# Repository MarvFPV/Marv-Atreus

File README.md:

# Marv Atreus
This is my first attempt at making a keyboard Pcb from scratch.
A Case will also be added.
Very much based on the https://github.com/technomancy/atreus.

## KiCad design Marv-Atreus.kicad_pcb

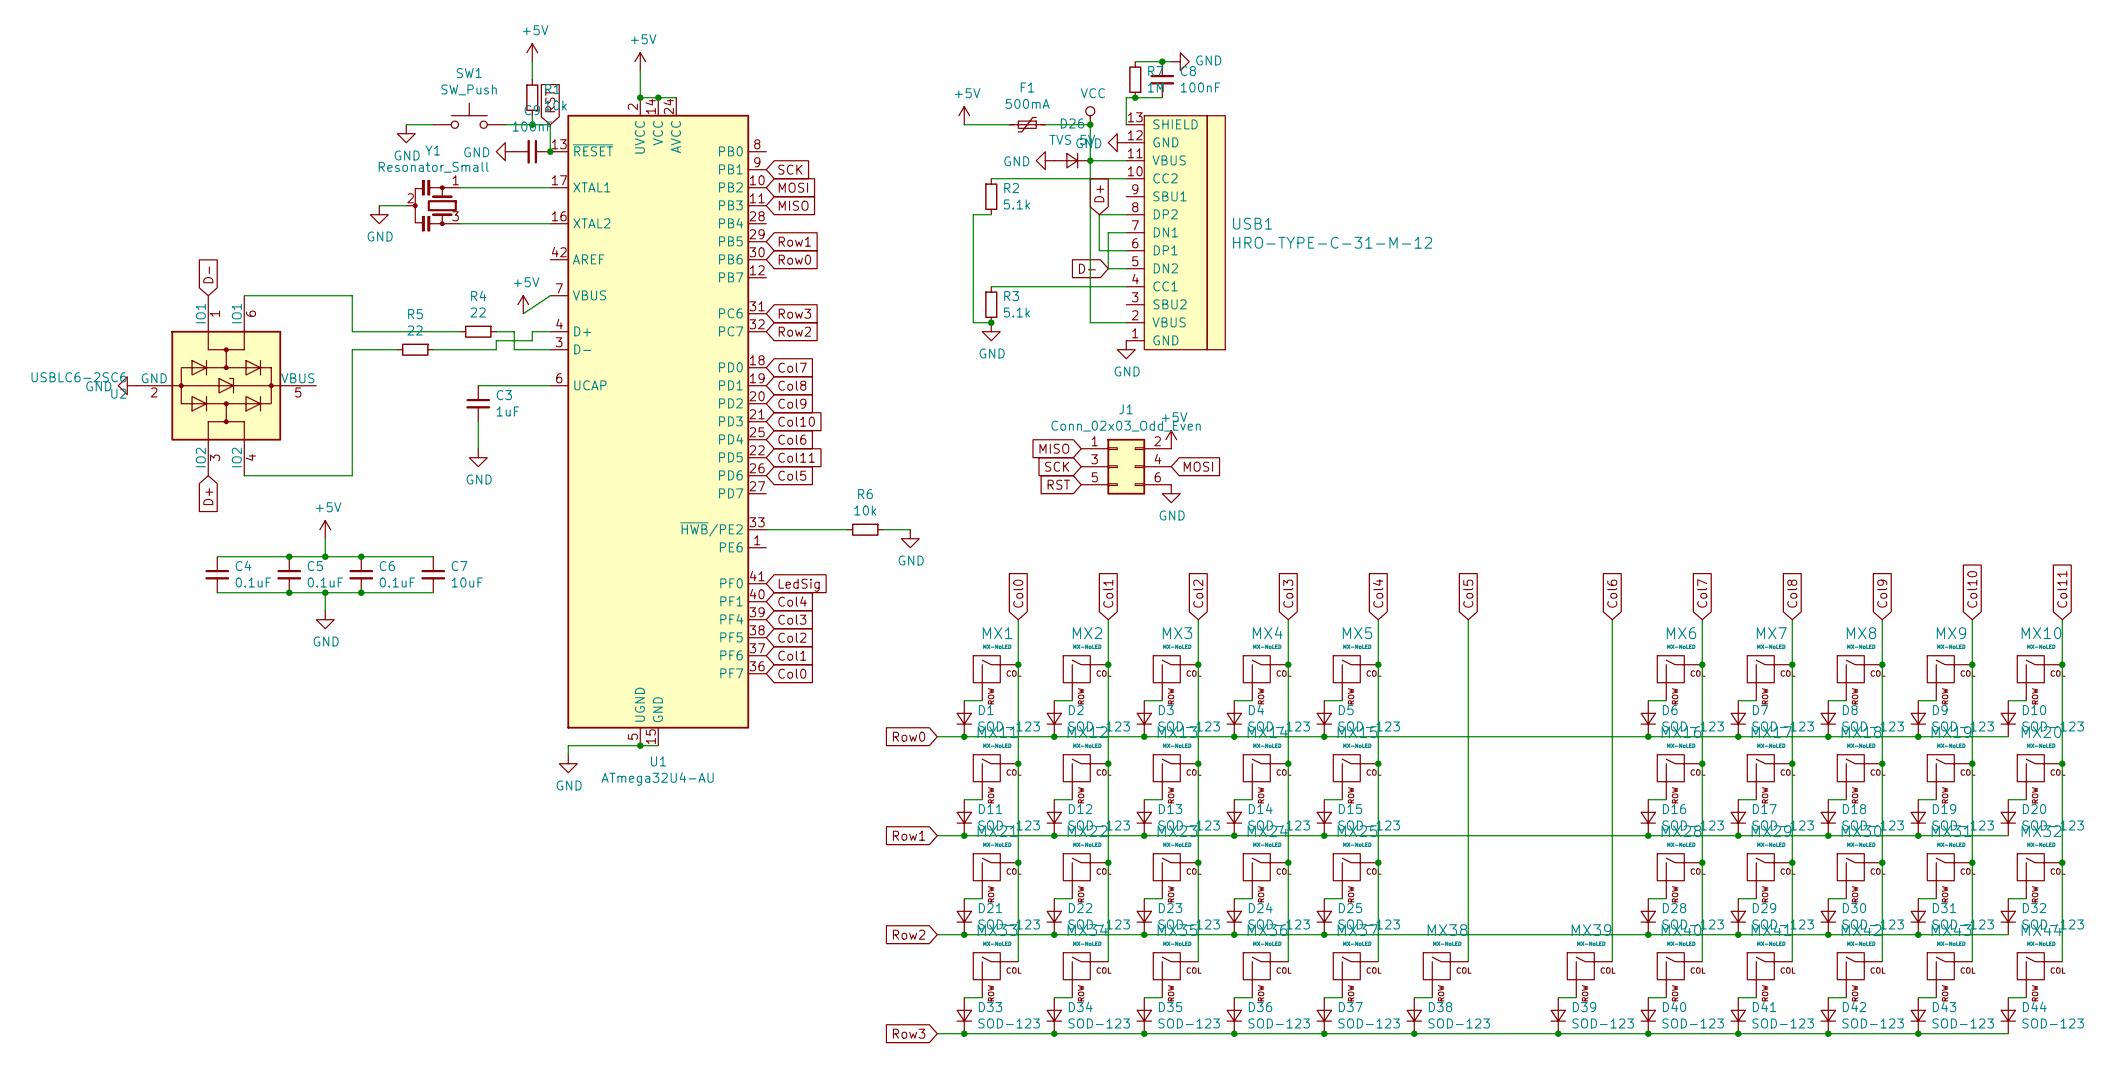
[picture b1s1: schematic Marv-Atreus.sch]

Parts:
C3: 1uF; C_0603_1608Metric
C4, C5, C6: 0.1uF; C_0603_1608Metric
C7: 10uF; C_0603_1608Metric
C8, C9: 100nF; C_0603_1608Metric
D1, D2, D3, D4, D5, D6, D7, D8, D9, D10, D11, D12, D13, D14, D15, D16, D17, D18, D19, D20, D21, D22, D23, D24, D25, D28, D29, D30, D31, D32, D33, D34, D35, D36, D37, D38, D39, D40, D41, D42, D43, D44: SOD-123; D_SOD-123_NoReference
D26: TVS 5V; D_SMB
F1: 500mA; Fuse_1206_3216Metric
J1: Conn_02x03_Odd_Even; PinHeader_2x03_P2.54mm_Vertical
MX1, MX2, MX3, MX4, MX5, MX6, MX7, MX8, MX9, MX10, MX11, MX12, MX13, MX14, MX15, MX16, MX17, MX18, MX19, MX20, MX21, MX22, MX23, MX24, MX25, MX28, MX29, MX30, MX31, MX32, MX33, MX34, MX35, MX36, MX37, MX38, MX39, MX40, MX41, MX42, MX43, MX44: MX-NoLED; MXOnly-1U-NoLED
R1, R6: 10k; R_0603_1608Metric
R2, R3: 5.1k; R_0603_1608Metric
R4, R5: 22; R_0603_1608Metric
R7: 1M; R_0603_1608Metric
SW1: SW_Push; SKQG-1155865
U1: ATmega32U4-AU; TQFP-44_10x10mm_P0.8mm
U2: USBLC6-2SC6; SOT-23-6
USB1: HRO-TYPE-C-31-M-12
Y1: Resonator_Small; Resonator_SMD_muRata_CSTxExxV-3Pin_3.0x1.1mm

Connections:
+5V: C4.1, C5.1, C6.1, C7.1, F1.2, J1.2, R1.1, U1.2 (UVCC), U1.7 (VBUS), U1.14 (VCC), U1.24 (AVCC), U1.34 (VCC), U1.44 (AVCC)
Col0: MX1.1 (COL), MX11.1 (COL), MX21.1 (COL), MX33.1 (COL), U1.36 (PF7)
Col1: MX2.1 (COL), MX12.1 (COL), MX22.1 (COL), MX34.1 (COL), U1.37 (PF6)
Col2: MX3.1 (COL), MX13.1 (COL), MX23.1 (COL), MX35.1 (COL), U1.38 (PF5)
Col3: MX4.1 (COL), MX14.1 (COL), MX24.1 (COL), MX36.1 (COL), U1.39 (PF4)
Col4: MX5.1 (COL), MX15.1 (COL), MX25.1 (COL), MX37.1 (COL), U1.40 (PF1)
Col5: MX38.1 (COL), U1.26 (PD6)
Col6: MX39.1 (COL), U1.25 (PD4)
Col7: MX6.1 (COL), MX16.1 (COL), MX28.1 (COL), MX40.1 (COL), U1.18 (PD0)
Col8: MX7.1 (COL), MX17.1 (COL), MX29.1 (COL), MX41.1 (COL), U1.19 (PD1)
Col9: MX8.1 (COL), MX18.1 (COL), MX30.1 (COL), MX42.1 (COL), U1.20 (PD2)
Col10: MX9.1 (COL), MX19.1 (COL), MX31.1 (COL), MX43.1 (COL), U1.21 (PD3)
Col11: MX10.1 (COL), MX20.1 (COL), MX32.1 (COL), MX44.1 (COL), U1.22 (PD5)
D+: U2.3 (IO2), USB1.6 (DP1), USB1.8 (DP2)
D-: U2.1 (IO1), USB1.5 (DN2), USB1.7 (DN1)
GND: C3.2, C4.2, C5.2, C6.2, C7.2, C8.1, C9.2, D26.2 (A), J1.6, R2.2, R3.2, R6.1, R7.2, SW1.1, U1.5 (UGND), U1.15 (GND), U1.23 (GND), U1.35 (GND), U1.43 (GND), U2.2 (GND), USB1.1 (GND), USB1.12 (GND), Y1.2
LedSig: U1.41 (PF0)
MISO: J1.1, U1.11 (PB3)
MOSI: J1.4, U1.10 (PB2)
unnamed: C3.1, U1.6 (UCAP)
unnamed: C8.2, R7.1, USB1.13 (SHIELD)
unnamed: D1.2 (A), MX1.2 (ROW)
unnamed: D2.2 (A), MX2.2 (ROW)
unnamed: D3.2 (A), MX3.2 (ROW)
unnamed: D4.2 (A), MX4.2 (ROW)
unnamed: D5.2 (A), MX5.2 (ROW)
unnamed: D6.2 (A), MX6.2 (ROW)
unnamed: D7.2 (A), MX7.2 (ROW)
unnamed: D8.2 (A), MX8.2 (ROW)
unnamed: D9.2 (A), MX9.2 (ROW)
unnamed: D10.2 (A), MX10.2 (ROW)
unnamed: D11.2 (A), MX11.2 (ROW)
unnamed: D12.2 (A), MX12.2 (ROW)
unnamed: D13.2 (A), MX13.2 (ROW)
unnamed: D14.2 (A), MX14.2 (ROW)
unnamed: D15.2 (A), MX15.2 (ROW)
unnamed: D16.2 (A), MX16.2 (ROW)
unnamed: D17.2 (A), MX17.2 (ROW)
unnamed: D18.2 (A), MX18.2 (ROW)
unnamed: D19.2 (A), MX19.2 (ROW)
unnamed: D20.2 (A), MX20.2 (ROW)
unnamed: D21.2 (A), MX21.2 (ROW)
unnamed: D22.2 (A), MX22.2 (ROW)
unnamed: D23.2 (A), MX23.2 (ROW)
unnamed: D24.2 (A), MX24.2 (ROW)
unnamed: D25.2 (A), MX25.2 (ROW)
unnamed: D28.2 (A), MX28.2 (ROW)
unnamed: D29.2 (A), MX29.2 (ROW)
unnamed: D30.2 (A), MX30.2 (ROW)
unnamed: D31.2 (A), MX31.2 (ROW)
unnamed: D32.2 (A), MX32.2 (ROW)
unnamed: D33.2 (A), MX33.2 (ROW)
unnamed: D34.2 (A), MX34.2 (ROW)
unnamed: D35.2 (A), MX35.2 (ROW)
unnamed: D36.2 (A), MX36.2 (ROW)
unnamed: D37.2 (A), MX37.2 (ROW)
unnamed: D38.2 (A), MX38.2 (ROW)
unnamed: D39.2 (A), MX39.2 (ROW)
unnamed: D40.2 (A), MX40.2 (ROW)
unnamed: D41.2 (A), MX41.2 (ROW)
unnamed: D42.2 (A), MX42.2 (ROW)
unnamed: D43.2 (A), MX43.2 (ROW)
unnamed: D44.2 (A), MX44.2 (ROW)
unnamed: R2.1, USB1.10 (CC2)
unnamed: R3.1, USB1.4 (CC1)
unnamed: R4.1, U1.3 (D-)
unnamed: R4.2, U2.6 (IO1)
unnamed: R5.1, U1.4 (D+)
unnamed: R5.2, U2.4 (IO2)
unnamed: R6.2, U1.33 (~HWB~/PE2)
unnamed: U1.16 (XTAL2), Y1.3
unnamed: U1.17 (XTAL1), Y1.1
RST: C9.1, J1.5, R1.2, SW1.2, U1.13 (~RESET)
Row0: D1.1 (K), D2.1 (K), D3.1 (K), D4.1 (K), D5.1 (K), D6.1 (K), D7.1 (K), D8.1 (K), D9.1 (K), D10.1 (K), U1.30 (PB6)
Row1: D11.1 (K), D12.1 (K), D13.1 (K), D14.1 (K), D15.1 (K), D16.1 (K), D17.1 (K), D18.1 (K), D19.1 (K), D20.1 (K), U1.29 (PB5)
Row2: D21.1 (K), D22.1 (K), D23.1 (K), D24.1 (K), D25.1 (K), D28.1 (K), D29.1 (K), D30.1 (K), D31.1 (K), D32.1 (K), U1.32 (PC7)
Row3: D33.1 (K), D34.1 (K), D35.1 (K), D36.1 (K), D37.1 (K), D38.1 (K), D39.1 (K), D40.1 (K), D41.1 (K), D42.1 (K), D43.1 (K), D44.1 (K), U1.31 (PC6)
SCK: J1.3, U1.9 (PB1)
VCC: D26.1 (K), F1.1, USB1.2 (VBUS), USB1.11 (VBUS)

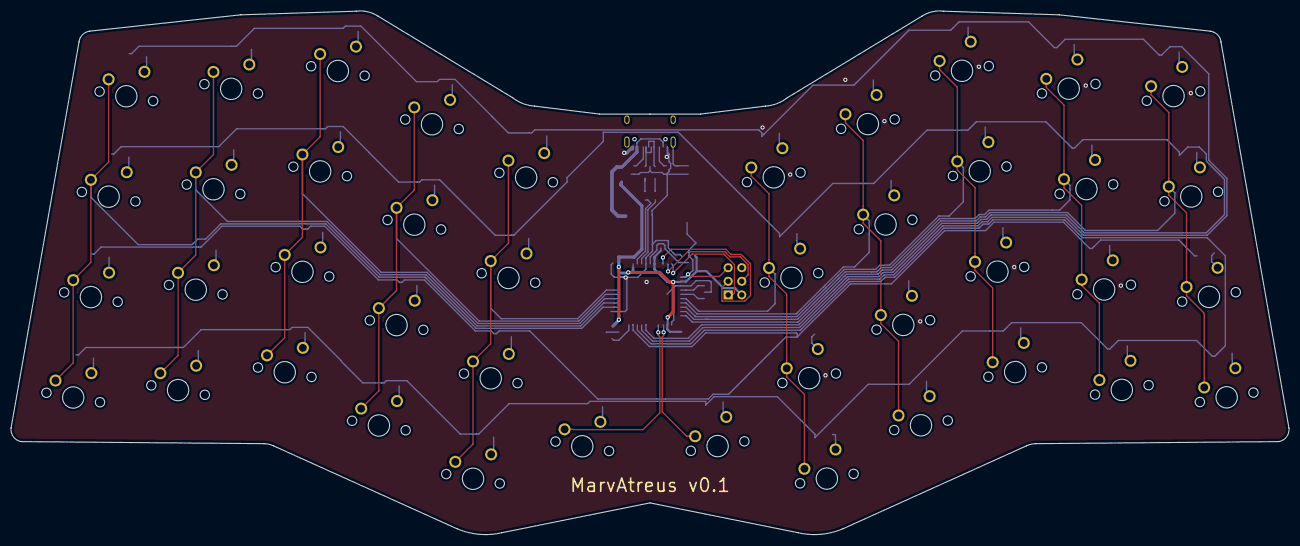
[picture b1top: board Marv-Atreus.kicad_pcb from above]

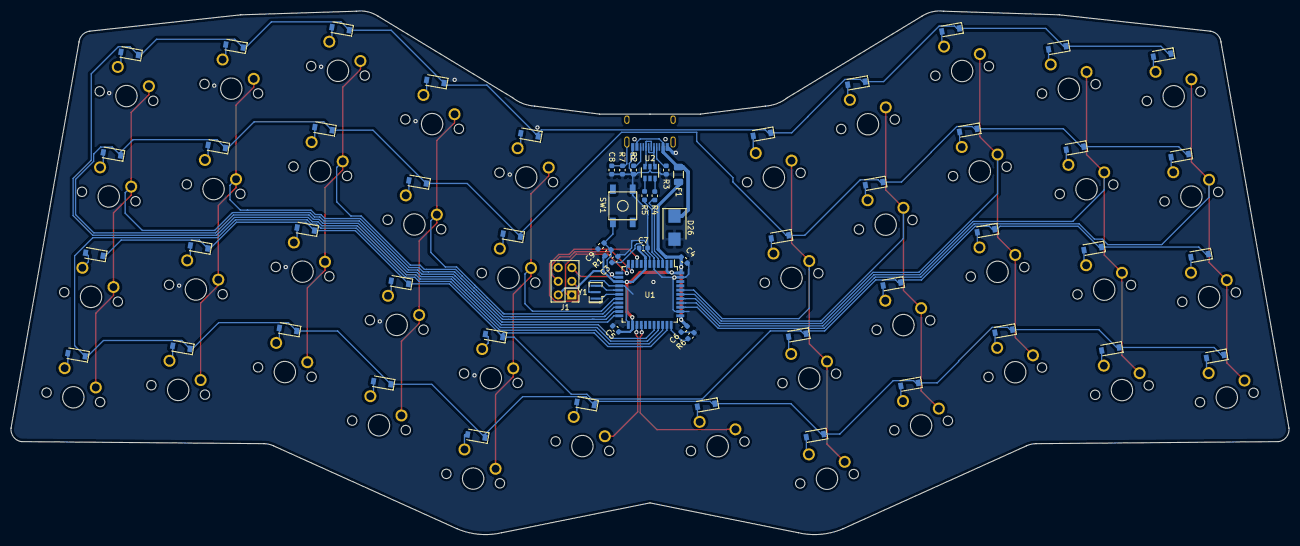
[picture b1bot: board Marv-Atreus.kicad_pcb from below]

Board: 2 copper layers, 238.8 x 97.8 mm, 106 parts (64 on the bottom side), 78 nets.

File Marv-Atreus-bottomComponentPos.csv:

Designator,Val,Package,Mid X,Mid Y,Rotation,Layer
C1,22pF,C_0603_1608Metric,151.2515,-108.123124,0,bottom
C2,22pF,C_0603_1608Metric,151.2515,-100.757124,180,bottom
C3,1uF,C_0603_1608Metric,145.967153,-97.984277,135,bottom
C4,0.1uF,C_0603_1608Metric,133.013153,-98.081971,225,bottom
C5,0.1uF,C_0603_1608Metric,145.810847,-110.938277,45,bottom
C6,0.1uF,C_0603_1608Metric,133.013153,-110.987124,315,bottom
C7,10uF,C_0603_1608Metric,139.3865,-96.255124,180,bottom
D1,SOD-123,D_SOD-123,43.969982,-61.704422,350,bottom
D2,SOD-123,D_SOD-123,63.557619,-60.322269,350,bottom
D3,SOD-123,D_SOD-123,83.489839,-56.985884,350,bottom
D4,SOD-123,D_SOD-123,101.078889,-66.938283,350,bottom
D5,SOD-123,D_SOD-123,118.736855,-76.499834,350,bottom
D6,SOD-123,D_SOD-123,162.173306,-76.580929,10,bottom
D7,SOD-123,D_SOD-123,179.762358,-66.62853,10,bottom
D8,SOD-123,D_SOD-123,197.454863,-56.760327,10,bottom
D9,SOD-123,D_SOD-123,217.283628,-60.012519,10,bottom
D10,SOD-123,D_SOD-123,236.871263,-61.394671,10,bottom
D11,SOD-123,D_SOD-123,40.661977,-80.465057,350,bottom
D12,SOD-123,D_SOD-123,60.249613,-79.082905,350,bottom
D13,SOD-123,D_SOD-123,80.181833,-75.746518,350,bottom
D14,SOD-123,D_SOD-123,97.770883,-85.698917,350,bottom
D15,SOD-123,D_SOD-123,115.359933,-95.651315,350,bottom
D16,SOD-123,D_SOD-123,165.481313,-95.341563,10,bottom
D17,SOD-123,D_SOD-123,183.070364,-85.389165,10,bottom
D18,SOD-123,D_SOD-123,200.659412,-75.436767,10,bottom
D19,SOD-123,D_SOD-123,220.591634,-78.773153,10,bottom
D20,SOD-123,D_SOD-123,240.17927,-80.155307,10,bottom
D21,SOD-123,D_SOD-123,36.963124,-99.156775,350,bottom
D22,SOD-123,D_SOD-123,56.941607,-97.843539,350,bottom
D23,SOD-123,D_SOD-123,76.873828,-94.507154,350,bottom
D24,SOD-123,D_SOD-123,94.462877,-104.459553,350,bottom
D25,SOD-123,D_SOD-123,112.120843,-114.021103,350,bottom
D28,SOD-123,D_SOD-123,168.789321,-114.102199,10,bottom
D29,SOD-123,D_SOD-123,186.37837,-104.1498,10,bottom
D30,SOD-123,D_SOD-123,203.967418,-94.197403,10,bottom
D31,SOD-123,D_SOD-123,223.899639,-97.533789,10,bottom
D32,SOD-123,D_SOD-123,243.487275,-98.915941,10,bottom
D33,SOD-123,D_SOD-123,34.045964,-117.986327,350,bottom
D34,SOD-123,D_SOD-123,53.6336,-116.604175,350,bottom
D35,SOD-123,D_SOD-123,73.565822,-113.267789,350,bottom
D36,SOD-123,D_SOD-123,91.154871,-123.220187,350,bottom
D37,SOD-123,D_SOD-123,108.812837,-132.781738,350,bottom
D38,SOD-123,D_SOD-123,129.158558,-127.100273,350,bottom
D39,SOD-123,D_SOD-123,151.682689,-126.790522,10,bottom
D40,SOD-123,D_SOD-123,172.097327,-132.862833,10,bottom
D41,SOD-123,D_SOD-123,189.686376,-122.910435,10,bottom
D42,SOD-123,D_SOD-123,207.275426,-112.958038,10,bottom
D43,SOD-123,D_SOD-123,227.207645,-116.294423,10,bottom
D44,SOD-123,D_SOD-123,246.795283,-117.676576,10,bottom
F1,500mA,Fuse_1206_3216Metric,134.332,-83.939124,270,bottom
R1,10k,R_0603_1608Metric,147.237153,-96.714277,135,bottom
R2,5.1k,R_0603_1608Metric,142.714,-83.162432,270,bottom
R3,5.1k,R_0603_1608Metric,136.618,-83.162432,270,bottom
R4,22,R_0603_1608Metric,140.682,-83.162432,90,bottom
R5,22,R_0603_1608Metric,138.65,-83.152624,90,bottom
R6,10k,R_0603_1608Metric,131.743153,-112.208277,315,bottom
SW1,SW_Push,SKQG-1155865,142.46,-90.159124,270,bottom
U1,ATmega32U4-AU,TQFP-44_10x10mm_P0.8mm,139.436693,-104.496232,270,bottom
USB1,HRO-TYPE-C-31-M-12,HRO-TYPE-C-31-M-12,139.652503,-71.158648,0,bottom
Y1,16MHz,Crystal_SMD_3225-4Pin_3.2x2.5mm,151.25244,-104.397124,90,bottom

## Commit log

2020-04-19 Project Initialization
2020-04-19 Add Submodules
2020-04-19 Added Kicad Libs
2020-04-19 Finalized Schematic/Added Footprints
2020-04-20 First Proto
2020-04-20 Added sth.
2020-04-21 Rerotued the board
2020-04-21 Complete reroute
2020-04-21 Small Updates
    - Decoupled USB Shield from GND
    - Cap to GND as a LPF for the RST button
    - Copper layer cleanup
    - Rounded PCB corners
2020-04-21 Small Update
    USB needed fixing
2020-04-21 OutlineCleanup for .stp export
2020-04-23 Even more Updates
    - switched from Crystal to resonator
    - added ESD protection ic
    - Cleaned up silkscreen
2020-04-23 Added ISP Connector
2020-04-23 Updates
    - Added TVS diode to vbus
    - Reinforced power lines
    - More cleanup
2020-04-23 Layout Updates
2020-04-23 v0.1
    Hopefully its a working pcb :baby_chick:
